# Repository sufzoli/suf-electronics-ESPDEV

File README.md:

# suf-electronics-ESPDEV
Development boards, programmers for Espressif ESP-8266, ESP-32, etc. chips/modules
The currently released boards:
HW/ESP_Prog - CH340G Based USB/Serial programmer. Single sided SMD for board house/home etch.
HW/ESP-01_Prog_SMD - ESP-01 SMD programming adapter for the serial programmer. Double sided for board house.
HW/ESP-01_Prog_THT - ESP-01 Trough hole programming adapter for the serial programmer. Single sided for home etch.
HW/ESP07S_Breakout_DS - ESP07S Double sided breakout for board house.
HW/ESP12E_Breakout_DS - ESP12E/F Double sided breakout for board house.
HW/ESP12E_Breakout_SS - ESP12E/F Single sided breakout for home etch.
HW/ESP12E_Breakout_SS_NP - ESP12E/F Single sided breakout for home etch. Programmer's connector not included

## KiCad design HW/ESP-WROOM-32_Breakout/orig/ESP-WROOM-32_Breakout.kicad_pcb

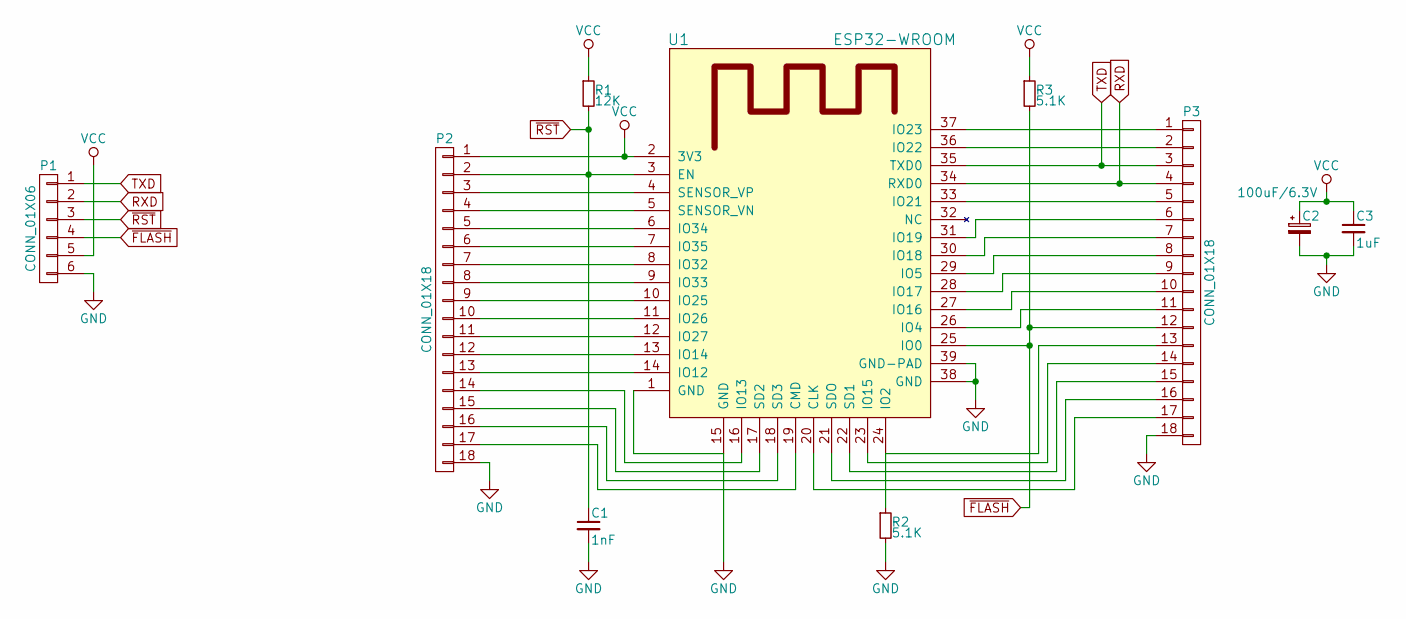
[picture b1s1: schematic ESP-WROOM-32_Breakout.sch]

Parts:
C1: 1nF; C_0603_HandSoldering
C2: 100uF/6.3V; CP_Tantalum_Case-B_EIA-3528-21_Hand
C3: 1uF; C_0603_HandSoldering
P1: CONN_01X06; ESP_ISP
P2, P3: CONN_01X18; Pin_Header_Straight_1x18_Pitch2.54mm
R1: 12K; R_0603_HandSoldering
R2, R3: 5.1K; R_0603_HandSoldering
U1: ESP32-WROOM; ESP-WROOM-32

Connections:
GND: C1.2, C2.2, C3.2, P1.6, P2.18, P3.18, R2.2, U1.1 (GND), U1.15 (GND), U1.38 (GND), U1.39 (GND-PAD)
unnamed: P2.3, U1.4 (SENSOR_VP)
unnamed: P2.4, U1.5 (SENSOR_VN)
unnamed: P2.5, U1.6 (IO34)
unnamed: P2.6, U1.7 (IO35)
unnamed: P2.7, U1.8 (IO32)
unnamed: P2.8, U1.9 (IO33)
unnamed: P2.9, U1.10 (IO25)
unnamed: P2.10, U1.11 (IO26)
unnamed: P2.11, U1.12 (IO27)
unnamed: P2.12, U1.13 (IO14)
unnamed: P2.13, U1.14 (IO12)
unnamed: P2.14, U1.16 (IO13)
unnamed: P2.15, U1.17 (SD2)
unnamed: P2.16, U1.18 (SD3)
unnamed: P2.17, U1.19 (CMD)
unnamed: P3.1, U1.37 (IO23)
unnamed: P3.2, U1.36 (IO22)
unnamed: P3.5, U1.33 (IO21)
unnamed: P3.6, U1.31 (IO19)
unnamed: P3.7, U1.30 (IO18)
unnamed: P3.8, U1.29 (IO5)
unnamed: P3.9, U1.28 (IO17)
unnamed: P3.10, U1.27 (IO16)
unnamed: P3.11, U1.26 (IO4)
unnamed: P3.13, R2.1, U1.24 (IO2)
unnamed: P3.14, U1.23 (IO15)
unnamed: P3.15, U1.22 (SD1)
unnamed: P3.16, U1.21 (SDO)
unnamed: P3.17, U1.20 (CLK)
RXD: P1.2, P3.4, U1.34 (RXD0)
TXD: P1.1, P3.3, U1.35 (TXD0)
VCC: C2.1, C3.1, P1.5, P2.1, R1.1, R3.1, U1.2 (3V3)
~FLASH: P1.4, P3.12, R3.2, U1.25 (IO0)
~RST: C1.1, P1.3, P2.2, R1.2, U1.3 (EN)

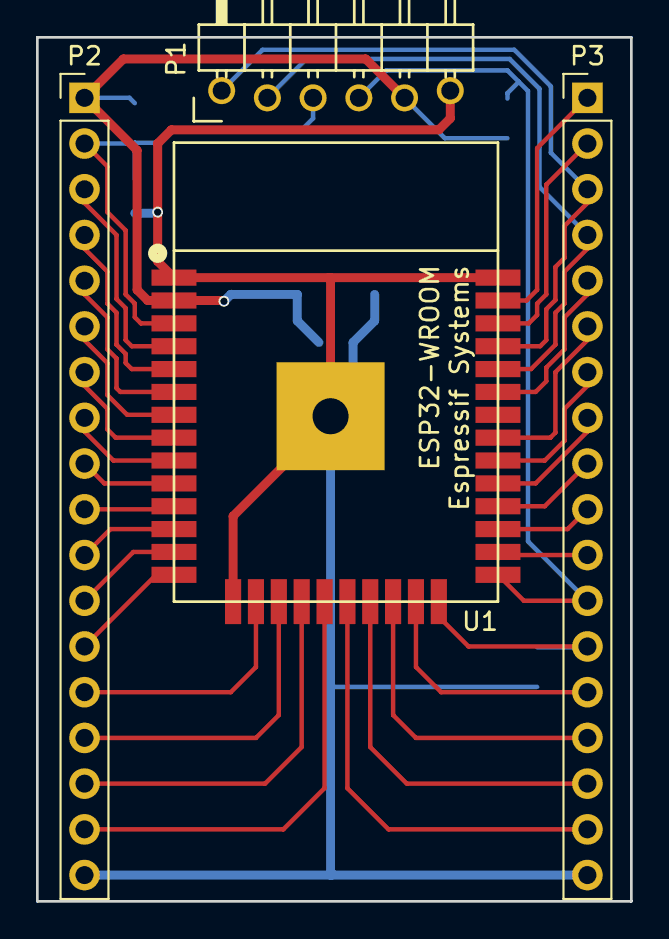
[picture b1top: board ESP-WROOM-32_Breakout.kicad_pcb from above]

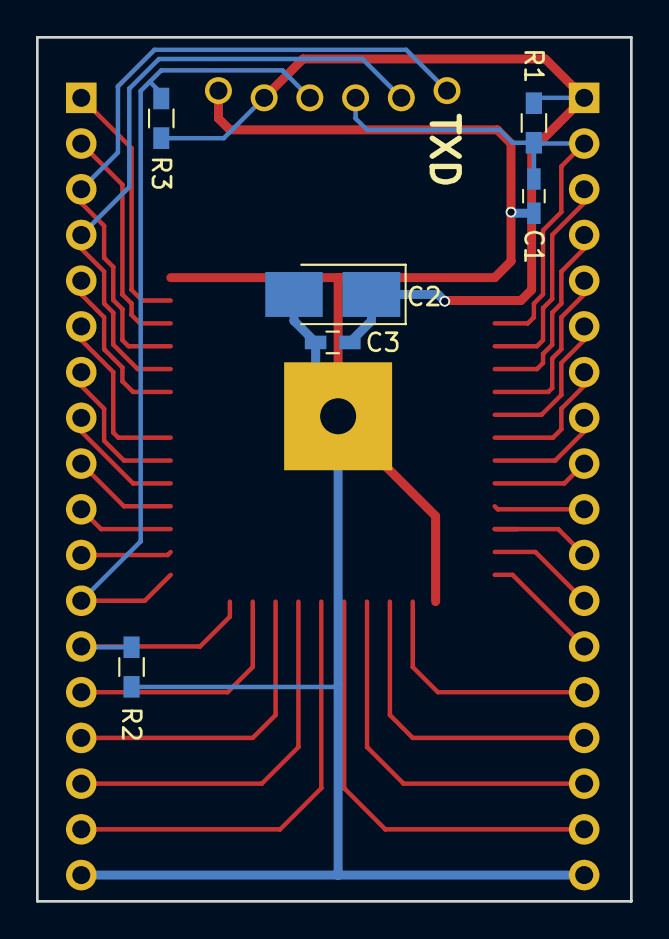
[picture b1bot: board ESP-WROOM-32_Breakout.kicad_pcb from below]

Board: 2 copper layers, 33.0 x 48.0 mm, 10 parts (6 on the bottom side), 35 nets.

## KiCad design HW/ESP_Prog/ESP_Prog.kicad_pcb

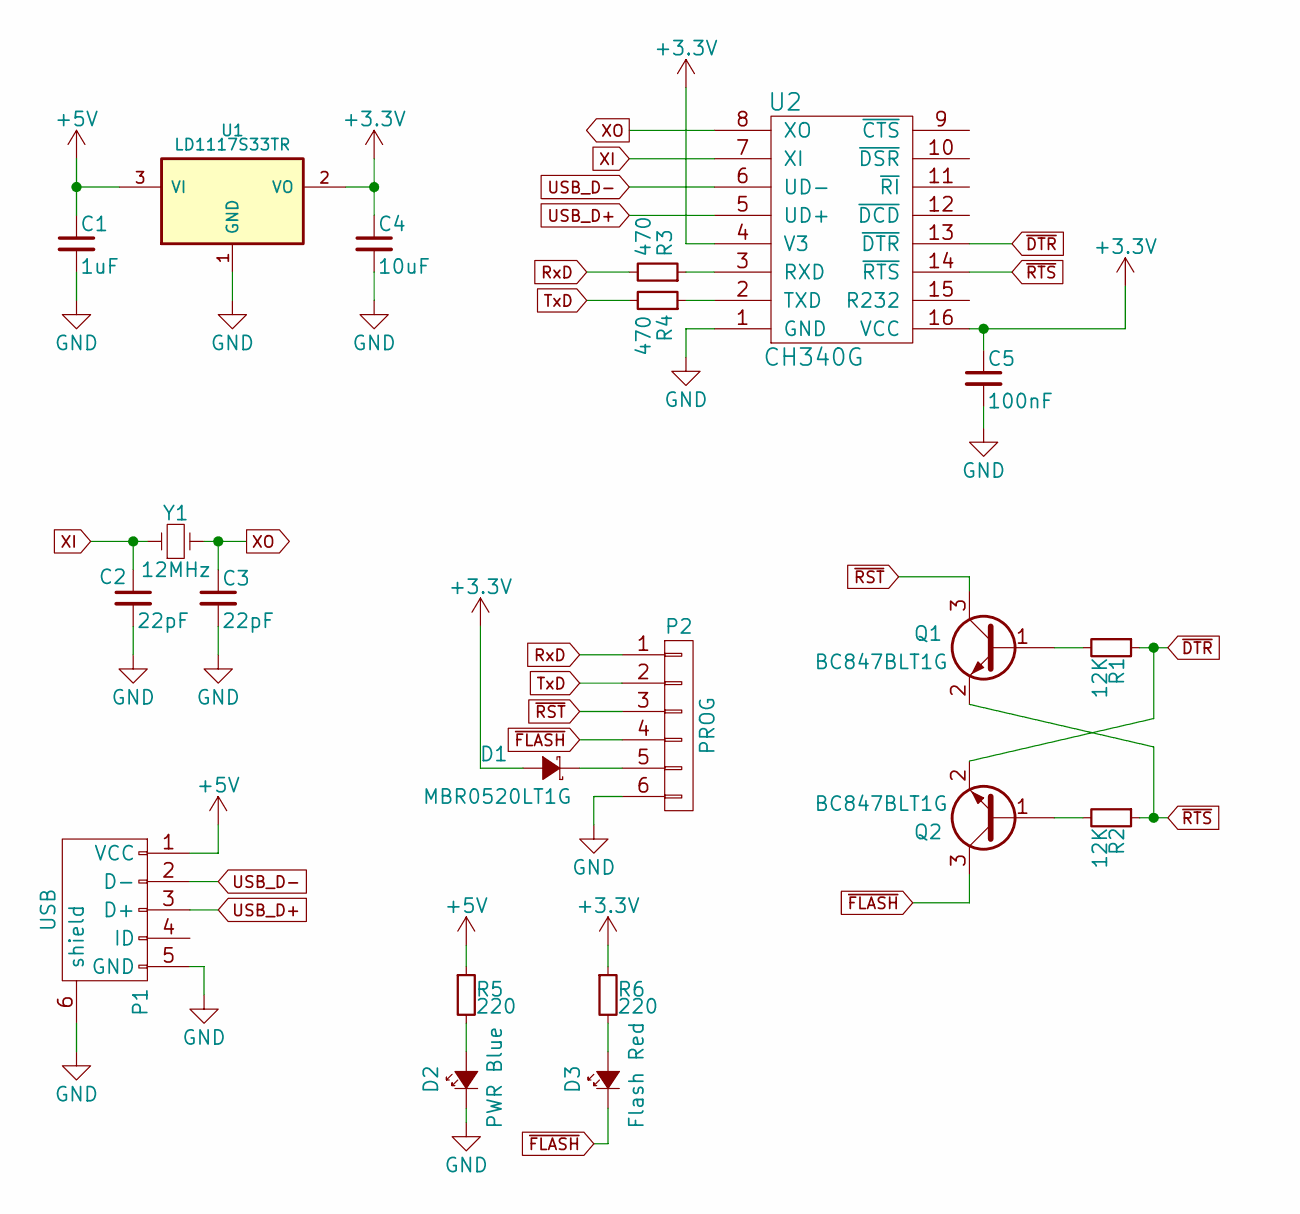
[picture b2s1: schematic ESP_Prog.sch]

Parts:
C1: 1uF; C_0603_HandSoldering
C2, C3: 22pF; C_0603_HandSoldering
C4: 10uF; C_0603_HandSoldering
C5: 100nF; C_0603_HandSoldering
D1: MBR0520LT1G; SOD-123
D2: PWR Blue; LED_0603
D3: Flash Red; LED_0603
P1: USB; USB_Mini-B
P2: PROG; Pin_Header_Angled_1x06
Q1, Q2: BC847BLT1G; SOT-23_Handsoldering
R1, R2: 12K; R_0603_HandSoldering
R3, R4: 470; R_0603_HandSoldering
R5, R6: 220; R_0603_HandSoldering
U1: LD1117S33TR; SOT-223
U2: CH340G; SOIC-16_3.9x9.9mm_Pitch1.27mm
Y1: 12MHz; Crystal_HC49-SD_SMD

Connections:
+3V3: C4.1, C5.1, D1.2 (A), R6.1, U1.2 (VO), U2.4 (V3), U2.16 (VCC)
+5V: C1.1, P1.1 (VCC), R5.1, U1.3 (VI)
GND: C1.2, C2.2, C3.2, C4.2, C5.2, D2.1 (K), P1.5 (GND), P1.6 (shield), P2.6, U1.1 (GND), U2.1 (GND)
unnamed: D1.1 (K), P2.5
unnamed: D2.2 (A), R5.2
unnamed: D3.2 (A), R6.2
unnamed: Q1.1 (B), R1.2
unnamed: Q2.1 (B), R2.2
unnamed: R3.1, U2.3 (RXD)
unnamed: R4.1, U2.2 (TXD)
RxD: P2.1, R3.2
TxD: P2.2, R4.2
USB_D+: P1.3 (D+), U2.5 (UD+)
USB_D-: P1.2 (D-), U2.6 (UD-)
XI: C2.1, U2.7 (XI), Y1.1
XO: C3.1, U2.8 (XO), Y1.2
~DTR: Q2.2 (E), R1.1, U2.13 (~DTR)
~FLASH: D3.1 (K), P2.4, Q2.3 (C)
~RST: P2.3, Q1.3 (C)
~RTS: Q1.2 (E), R2.1, U2.14 (~RTS)

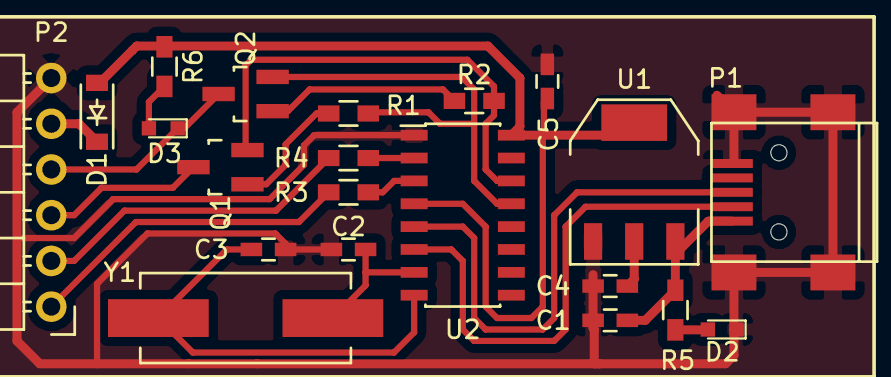
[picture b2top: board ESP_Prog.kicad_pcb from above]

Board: 2 copper layers, 21 parts (0 on the bottom side), 20 nets.

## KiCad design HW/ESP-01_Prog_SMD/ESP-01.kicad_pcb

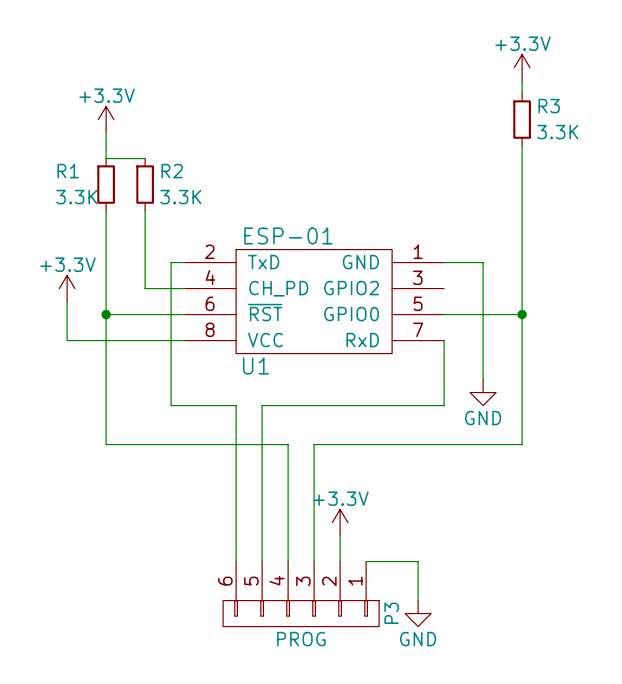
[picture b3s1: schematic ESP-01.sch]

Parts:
P3: PROG; Pin_Header_Straight_1x06_Pitch2.54mm
R1, R2, R3: 3.3K; R_0603_HandSoldering
U1: ESP-01

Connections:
+3V3: P3.2, R1.1, R2.1, R3.1, U1.8 (VCC)
GND: P3.1, U1.1 (GND)
unnamed: P3.3, R3.2, U1.5 (GPIO0)
unnamed: P3.4, R1.2, U1.6 (~RST)
unnamed: P3.5, U1.7 (RxD)
unnamed: P3.6, U1.2 (TxD)
unnamed: R2.2, U1.4 (CH_PD)

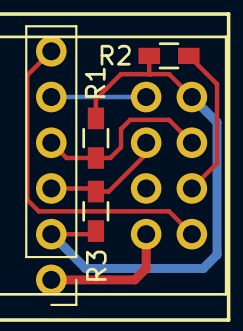
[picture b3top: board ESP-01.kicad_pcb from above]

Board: 2 copper layers, 5 parts (0 on the bottom side), 7 nets.

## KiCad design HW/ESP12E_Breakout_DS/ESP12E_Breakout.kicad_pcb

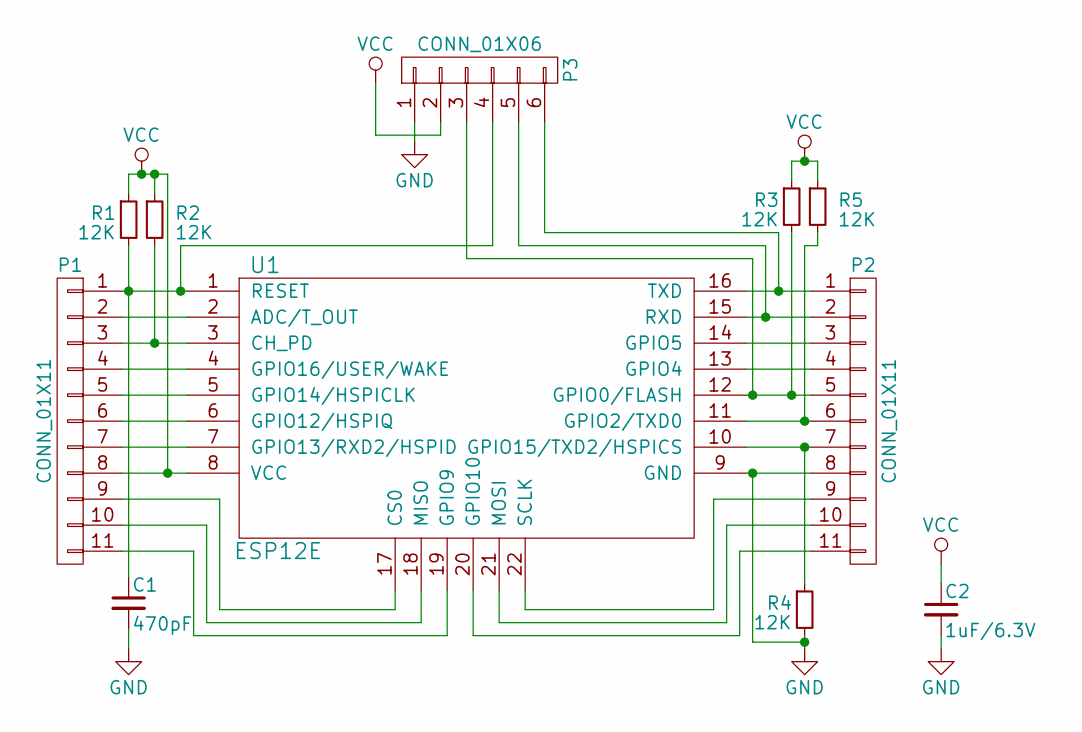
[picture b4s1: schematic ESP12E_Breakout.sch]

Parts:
C1: 470pF; C_0603_HandSoldering
C2: 1uF/6.3V; C_0603_HandSoldering
P1, P2: CONN_01X11; Pin_Header_Straight_1x11
P3: CONN_01X06; Pin_Header_Angled_1x06
R1, R2, R3, R4, R5: 12K; R_0603_HandSoldering
U1: ESP12E; ESP-12E

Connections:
GND: C1.2, C2.2, P2.8, P3.1, R4.2, U1.9 (GND)
unnamed: C1.1, P1.1, P3.4, R1.2, U1.1 (RESET)
unnamed: P1.2, U1.2 (ADC/T_OUT)
unnamed: P1.3, R2.2, U1.3 (CH_PD)
unnamed: P1.4, U1.4 (GPIO16/USER/WAKE)
unnamed: P1.5, U1.5 (GPIO14/HSPICLK)
unnamed: P1.6, U1.6 (GPIO12/HSPIQ)
unnamed: P1.7, U1.7 (GPIO13/RXD2/HSPID)
unnamed: P1.9, U1.17 (CS0)
unnamed: P1.10, U1.18 (MISO)
unnamed: P1.11, U1.19 (GPIO9)
unnamed: P2.1, P3.6, U1.16 (TXD)
unnamed: P2.2, P3.5, U1.15 (RXD)
unnamed: P2.3, U1.14 (GPIO5)
unnamed: P2.4, U1.13 (GPIO4)
unnamed: P2.5, P3.3, R3.2, U1.12 (GPIO0/FLASH)
unnamed: P2.6, R5.2, U1.11 (GPIO2/TXD0)
unnamed: P2.7, R4.1, U1.10 (GPIO15/TXD2/HSPICS)
unnamed: P2.9, U1.22 (SCLK)
unnamed: P2.10, U1.21 (MOSI)
unnamed: P2.11, U1.20 (GPIO10)
VCC: C2.1, P1.8, P3.2, R1.1, R2.1, R3.1, R5.1, U1.8 (VCC)

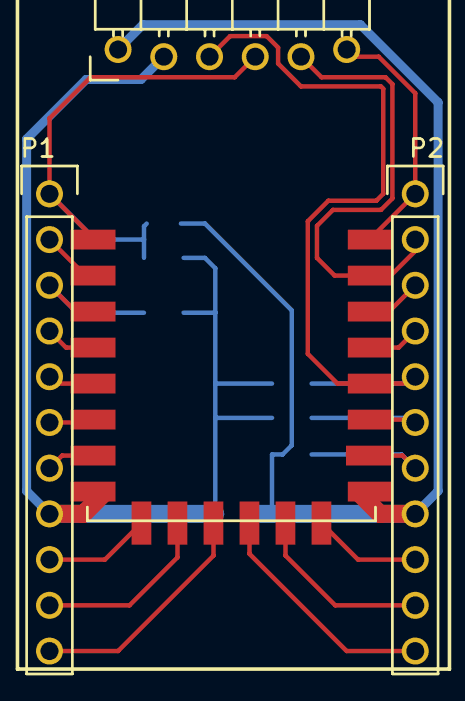
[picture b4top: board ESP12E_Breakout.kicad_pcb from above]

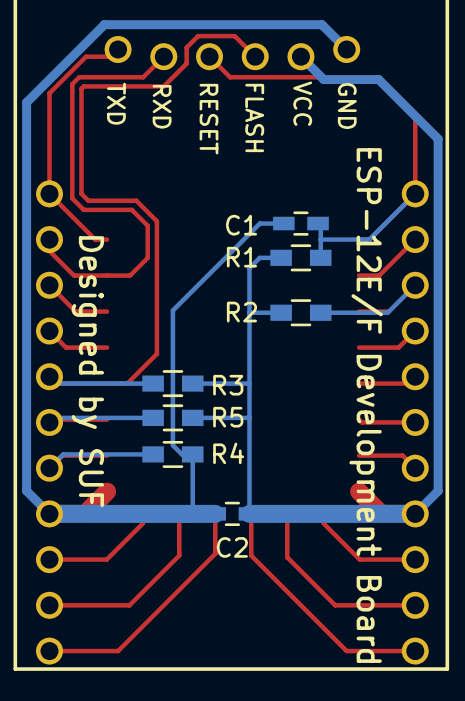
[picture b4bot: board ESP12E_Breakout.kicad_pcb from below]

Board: 2 copper layers, 11 parts (7 on the bottom side), 22 nets.

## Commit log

2017-03-25 Serial Programmer and ESP8266 boards/adapters added
2017-04-03 ESP32 Dev board added
2021-03-20 Modify ESP-32 Breakout
